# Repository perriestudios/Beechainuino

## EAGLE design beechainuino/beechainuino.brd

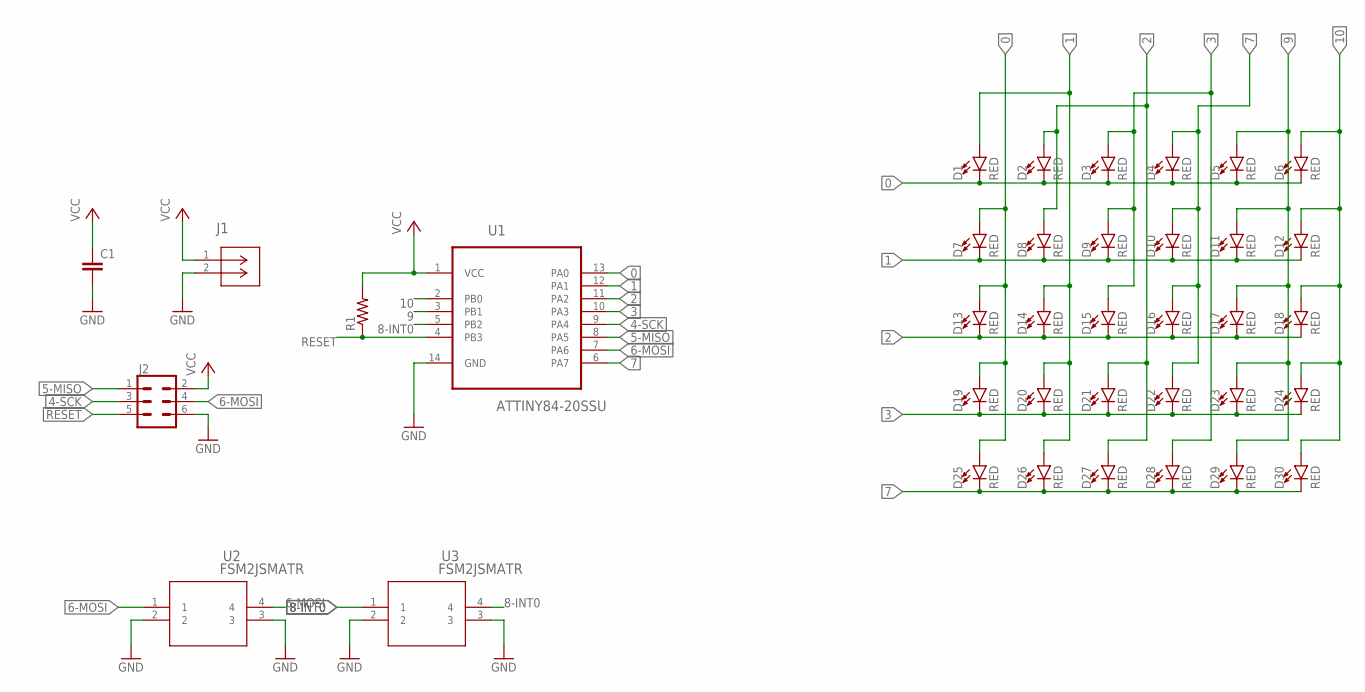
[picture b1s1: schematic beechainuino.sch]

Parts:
C1: C-EUC0603K; C0603K
D1, D2, D3, D4, D5, D6, D7, D8, D9, D10, D11, D12, D13, D14, D15, D16, D17, D18, D19, D20, D21, D22, D23, D24, D25, D26, D27, D28, D29, D30: RED; LED-0603
J1: 796136-1; CON2_BATT-HOLDER_SMT
J2: CONN_03X2FEMALE_SMD; 2X3_SMD
R1: R-US_R0603; R0603
U1: ATTINY84-20SSU; SOIC127P600X175-14N
U2, U3: FSM2JSMATR; SWITCH_FSM2JSMAA

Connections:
0: D1.C, D2.C, D3.C, D4.C, D5.C, D6.C, D7.A, D13.A, D19.A, D25.A, U1.13 (PA0)
1: D1.A, D7.C, D8.C, D9.C, D10.C, D11.C, D12.C, D14.A, D20.A, D26.A, U1.12 (PA1)
2: D2.A, D8.A, D13.C, D14.C, D15.C, D16.C, D17.C, D18.C, D21.A, D27.A, U1.11 (PA2)
3: D3.A, D9.A, D15.A, D19.C, D20.C, D21.C, D22.C, D23.C, D24.C, D28.A, U1.10 (PA3)
4-SCK: J2.3, U1.9 (PA4)
5-MISO: J2.1, U1.8 (PA5)
6-MOSI: J2.4, U1.7 (PA6), U2.1, U2.4
7: D4.A, D10.A, D16.A, D22.A, D25.C, D26.C, D27.C, D28.C, D29.C, D30.C, U1.6 (PA7)
8-INT0: U1.5 (PB2), U3.1, U3.4
9: D5.A, D11.A, D17.A, D23.A, D29.A, U1.3 (PB1)
10: D6.A, D12.A, D18.A, D24.A, D30.A, U1.2 (PB0)
GND: C1.2, J1.2, J2.6, U1.14 (GND), U2.2, U2.3, U3.2, U3.3
RESET: J2.5, R1.1, U1.4 (PB3)
VCC: C1.1, J1.1, J2.2, R1.2, U1.1 (VCC)

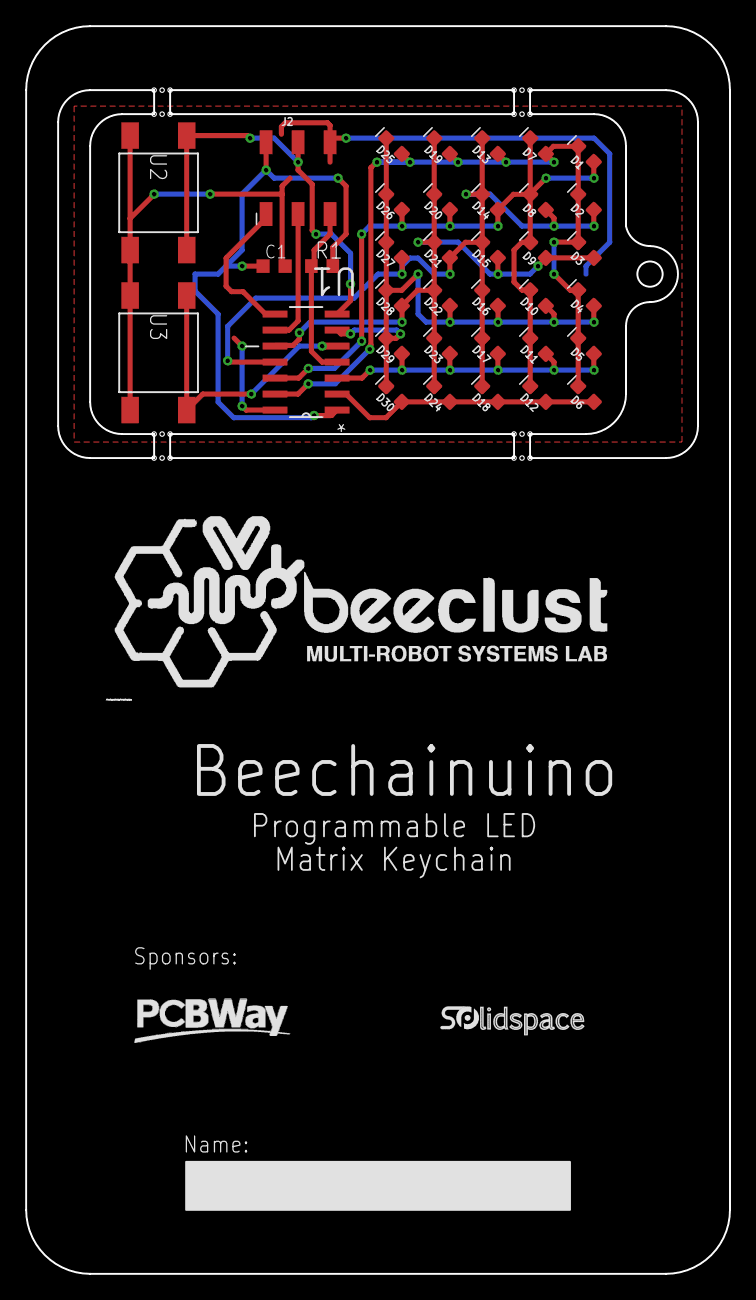
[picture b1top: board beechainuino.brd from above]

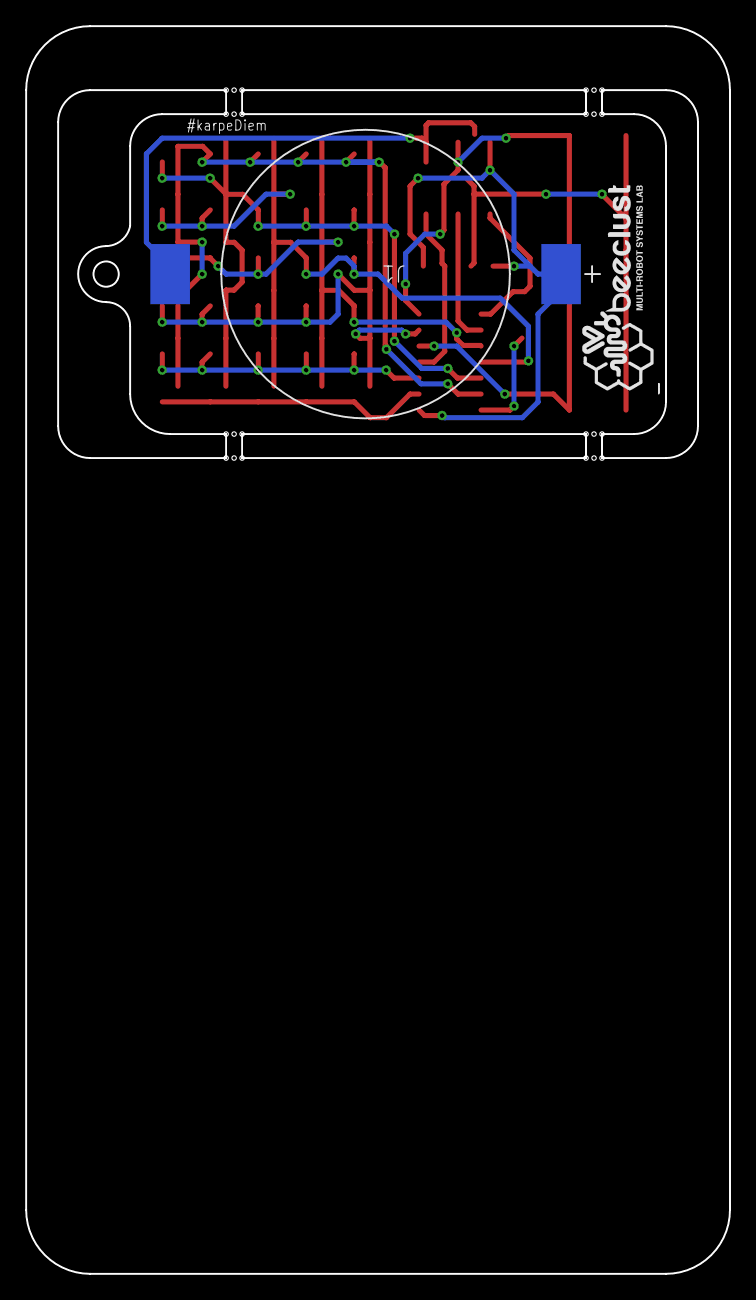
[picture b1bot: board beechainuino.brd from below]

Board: 2 copper layers, 55.9 x 99.1 mm, 41 parts (2 on the bottom side), 14 nets.

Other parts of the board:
U$1: PCBWAYLOGO-M
U$2: LOGO-M
U$3: SOLIDSPACELOGO-M
U$4: LOGO-L

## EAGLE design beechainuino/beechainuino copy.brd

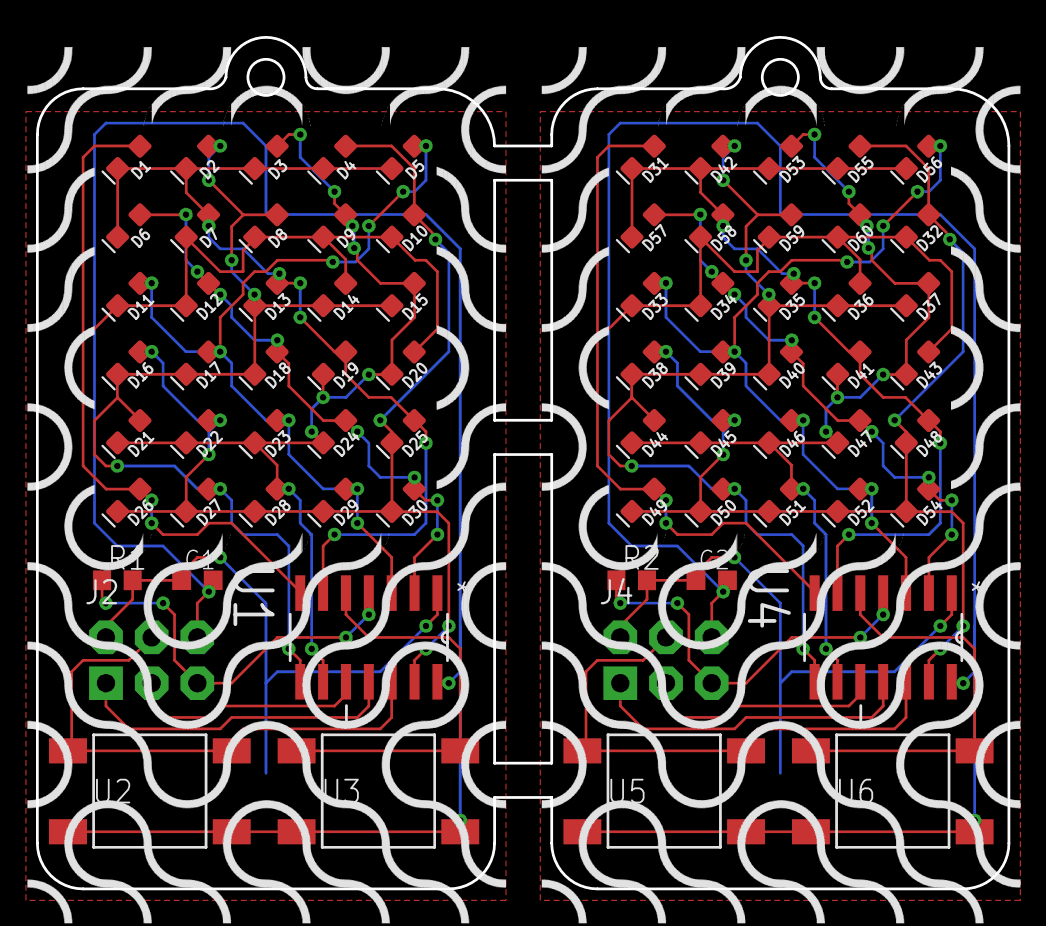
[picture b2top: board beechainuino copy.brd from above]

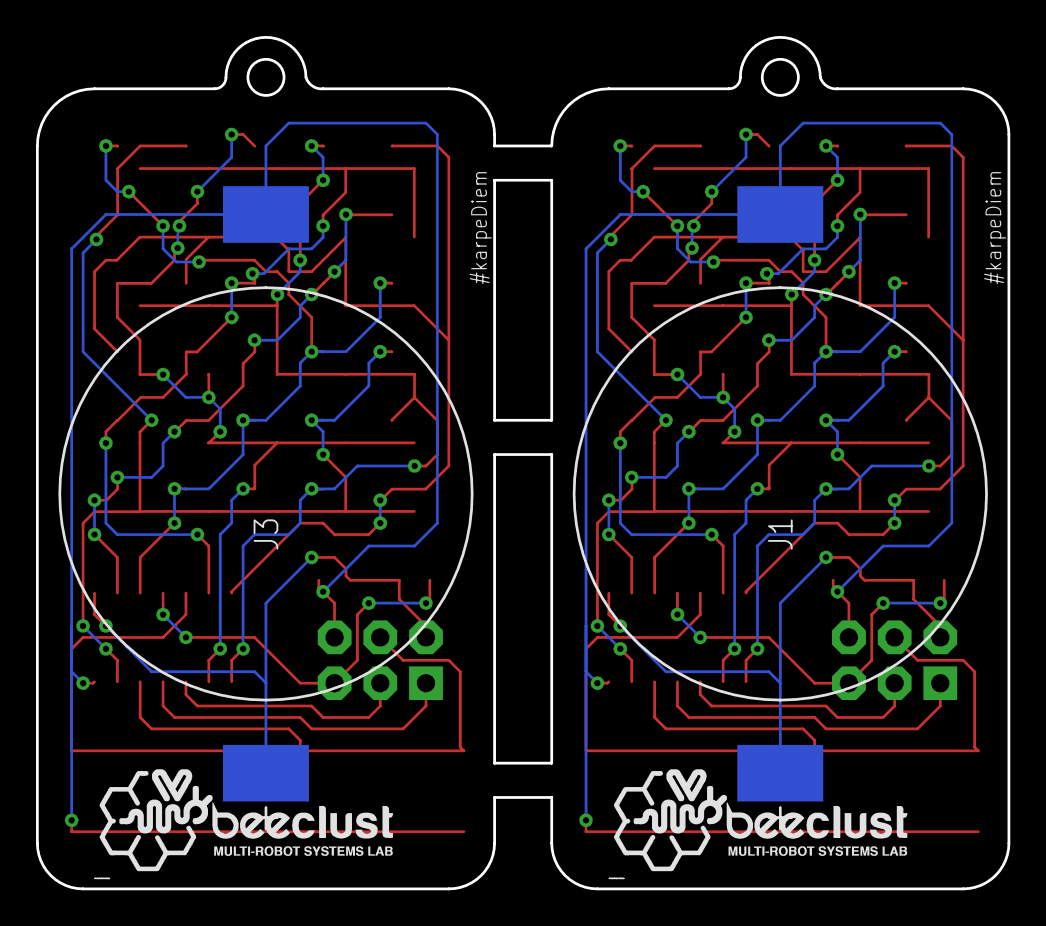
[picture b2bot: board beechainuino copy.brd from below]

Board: 2 copper layers, 54.0 x 47.3 mm, 78 parts (4 on the bottom side), 28 nets.

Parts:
C1, C2: C0603K
D1, D2, D3, D4, D5, D6, D7, D8, D9, D10, D11, D12, D13, D14, D15, D16, D17, D18, D19, D20, D21, D22, D23, D24, D25, D26, D27, D28, D29, D30, D31, D32, D33, D34, D35, D36, D37, D38, D39, D40, D41, D42, D43, D44, D45, D46, D47, D48, D49, D50, D51, D52, D53, D54, D55, D56, D57, D58, D59, D60: RED; LED-0603
J1, J3: 796136-1; CON2_BATT-HOLDER_SMT
J2, J4: AVR_SPI_PRG_6NS; 2X3-NS
R1, R2: R0603
U1, U4: ATTINY84-20SSU; SOIC127P600X175-14N
U2, U3, U5, U6: FSM2JSMATR; SWITCH_FSM2JSMAA
U$1, U$4: TRUCHET
U$2, U$3: LOGO-M

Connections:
0: D1.C, D2.C, D3.C, D4.C, D5.C, D6.C, D7.A, D13.A, D19.A, D25.A, U1.6
1: D1.A, D7.C, D8.C, D9.C, D10.C, D11.C, D12.C, D14.A, D20.A, D26.A, U1.7
2: D2.A, D8.A, D13.C, D14.C, D15.C, D16.C, D17.C, D18.C, D21.A, D27.A, U1.8
3: D3.A, D9.A, D15.A, D19.C, D20.C, D21.C, D22.C, D23.C, D24.C, D28.A, U1.9
4: D31.C, D35.A, D41.A, D42.C, D48.A, D53.C, D55.C, D56.C, D57.C, D58.A, U4.6
4-SCK: J2.3, U1.10
4-SCK1: J4.3, U4.10
5: D37.A, D41.C, D43.C, D44.C, D45.C, D46.C, D47.C, D51.A, D53.A, D60.A, U4.9
5-MISO: J2.1, U1.11
5-MISO1: J4.1, U4.11
6: D33.A, D39.A, D46.A, D52.A, D56.A, U4.3
6-MOSI: J2.4, U1.12, U2.1, U2.4
6-MOSI1: J4.4, U4.12, U5.1, U5.4
7: D4.A, D10.A, D16.A, D22.A, D25.C, D26.C, D27.C, D28.C, D29.C, D30.C, U1.13
8: D34.A, D40.A, D47.A, D54.A, D57.A, U4.2
8-INT0: U1.5, U3.1, U3.4
8-INT1: U4.5, U6.1, U6.4
9: D5.A, D11.A, D17.A, D23.A, D29.A, U1.3
10: D6.A, D12.A, D18.A, D24.A, D30.A, U1.2
11: D32.A, D38.A, D45.A, D48.C, D49.C, D50.C, D51.C, D52.C, D54.C, D55.A, U4.13
12: D31.A, D32.C, D33.C, D34.C, D36.A, D43.A, D49.A, D58.C, D59.C, D60.C, U4.7
13: D35.C, D36.C, D37.C, D38.C, D39.C, D40.C, D42.A, D44.A, D50.A, D59.A, U4.8
GND: C1.2, J1.2, J2.6, U1.14, U2.2, U2.3, U3.2, U3.3
GND1: C2.2, J3.2, J4.6, U4.14, U5.2, U5.3, U6.2, U6.3
RESET: J2.5, R1.1, U1.4
RESET1: J4.5, R2.1, U4.4
VCC: C1.1, J1.1, J2.2, R1.2, U1.1
VCC1: C2.1, J3.1, J4.2, R2.2, U4.1

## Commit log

2020-11-17 Added the files

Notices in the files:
parts and their libraries:
SparkFun-LED: Licensing: Creative Commons ShareAlike 4.0 International - https://creativecommons.org/licenses/by-sa/4.0
